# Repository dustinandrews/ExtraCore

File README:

http://authenticinvention.com/ExtraCore/
http://www.facebook.com/pages/ExtraCore-Arduino-Compatible/262175783799966

These are the Eagle files for the ExtraCore circuit board. 
License: Attribution-ShareAlike 3.0 Unported (CC BY-SA 3.0) 
http://creativecommons.org/licenses/by-sa/3.0/

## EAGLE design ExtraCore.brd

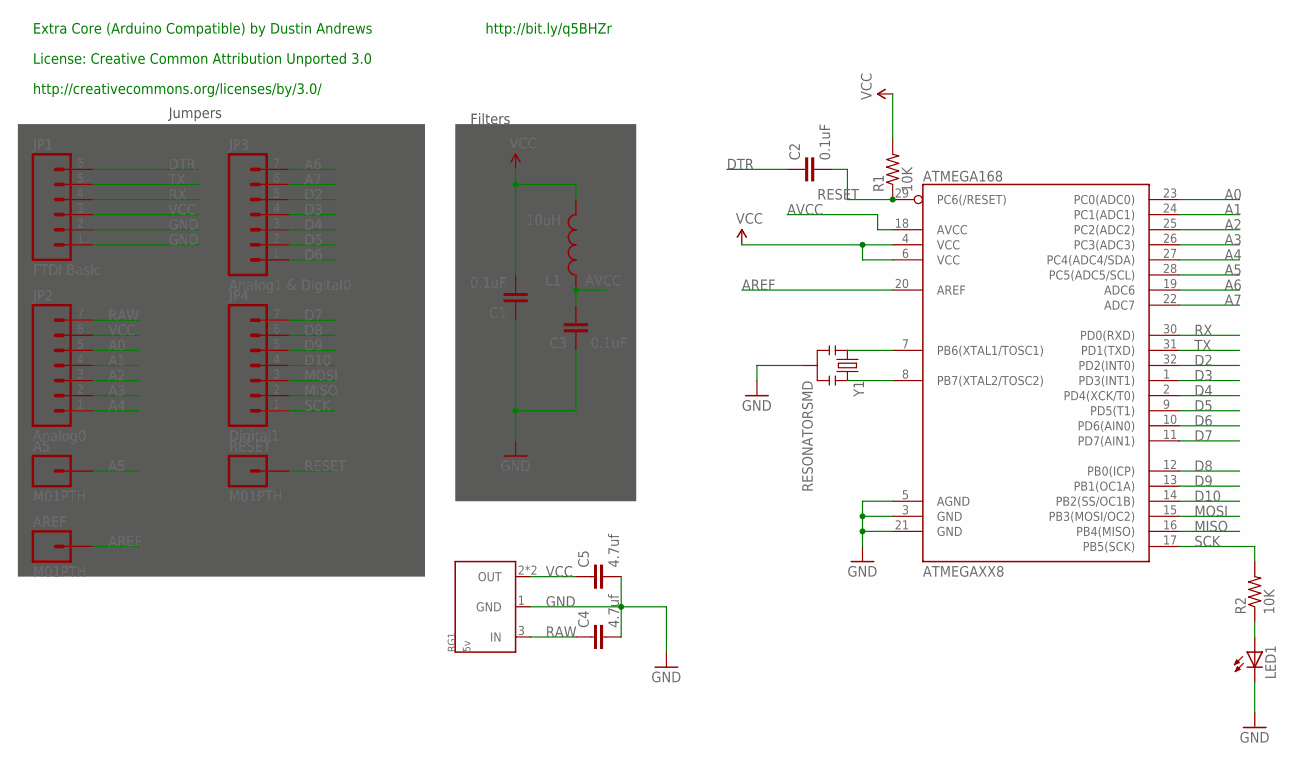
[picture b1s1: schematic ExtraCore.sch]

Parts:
A5: M01PTH; 1X01
AREF: M01PTH; 1X01
ATMEGAXX8: ATMEGA168; TQFP32-08
C1, C2, C3: 0.1uF; 0805
C4, C5: 4.7uf; 0805
JP1: FTDI Basic; 1X06
JP2: Analog0; 1X07
JP3: Analog1 & Digital0; 1X07
JP4: Digital1; 1X07
L1: 10uH; 0805
LED1: LED0805; LED-0805
R1, R2: 10K; 0805
RESET: M01PTH; 1X01
RG1: 5v; SOT223
Y1: RESONATORSMD; RESONATOR-SMD

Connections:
A0: ATMEGAXX8.23 (PC0(ADC0)), JP2.5
A1: ATMEGAXX8.24 (PC1(ADC1)), JP2.4
A2: ATMEGAXX8.25 (PC2(ADC2)), JP2.3
A3: ATMEGAXX8.26 (PC3(ADC3)), JP2.2
A4: ATMEGAXX8.27 (PC4(ADC4/SDA)), JP2.1
A5: A5.1, ATMEGAXX8.28 (PC5(ADC5/SCL))
A6: ATMEGAXX8.19 (ADC6), JP3.7
A7: ATMEGAXX8.22 (ADC7), JP3.6
AREF: AREF.1, ATMEGAXX8.20 (AREF)
AVCC: ATMEGAXX8.18 (AVCC), C3.2, L1.1
D2: ATMEGAXX8.32 (PD2(INT0)), JP3.5
D3: ATMEGAXX8.1 (PD3(INT1)), JP3.4
D4: ATMEGAXX8.2 (PD4(XCK/T0)), JP3.3
D5: ATMEGAXX8.9 (PD5(T1)), JP3.2
D6: ATMEGAXX8.10 (PD6(AIN0)), JP3.1
D7: ATMEGAXX8.11 (PD7(AIN1)), JP4.7
D8: ATMEGAXX8.12 (PB0(ICP)), JP4.6
D9: ATMEGAXX8.13 (PB1(OC1A)), JP4.5
D10: ATMEGAXX8.14 (PB2(SS/OC1B)), JP4.4
DTR: C2.1, JP1.6
GND: ATMEGAXX8.3 (GND), ATMEGAXX8.5 (AGND), ATMEGAXX8.21 (GND), C1.1, C3.1, C4.2, C5.2, JP1.1, JP1.2, LED1.C, RG1.1 (GND), Y1.2
MISO: ATMEGAXX8.16 (PB4(MISO)), JP4.2
MOSI: ATMEGAXX8.15 (PB3(MOSI/OC2)), JP4.3
unnamed: ATMEGAXX8.7 (PB6(XTAL1/TOSC1)), Y1.1
unnamed: ATMEGAXX8.8 (PB7(XTAL2/TOSC2)), Y1.3
unnamed: LED1.A, R2.1
RAW: C4.1, JP2.7, RG1.3 (IN)
RESET: ATMEGAXX8.29 (PC6(/RESET)), C2.2, R1.1, RESET.1
RX: ATMEGAXX8.30 (PD0(RXD)), JP1.4
SCK: ATMEGAXX8.17 (PB5(SCK)), JP4.1, R2.2
TX: ATMEGAXX8.31 (PD1(TXD)), JP1.5
VCC: ATMEGAXX8.4 (VCC), ATMEGAXX8.6 (VCC), C1.2, C5.1, JP1.3, JP2.6, L1.2, R1.2, RG1.2 (OUT), RG1.TAB (OUT)

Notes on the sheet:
http://creativecommons.org/licenses/by/3.0/
License: Creative Common Attribution Unported 3.0
Jumpers
Filters
Extra Core (Arduino Compatible) by Dustin Andrews
http://bit.ly/q5BHZr

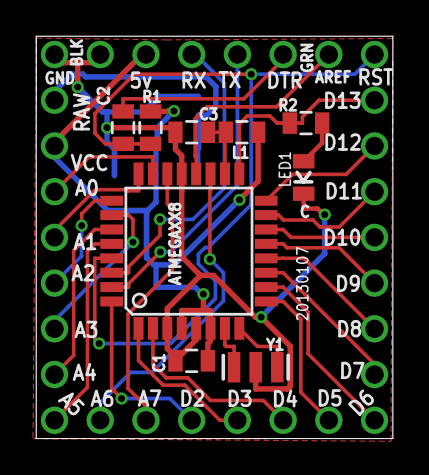
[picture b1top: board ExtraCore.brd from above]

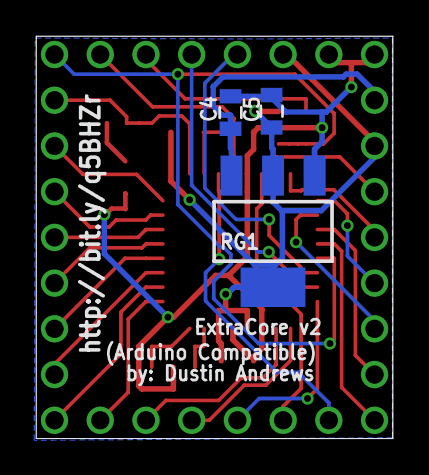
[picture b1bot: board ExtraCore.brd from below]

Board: 2 copper layers, 19.8 x 22.4 mm, 19 parts (3 on the bottom side), 32 nets.

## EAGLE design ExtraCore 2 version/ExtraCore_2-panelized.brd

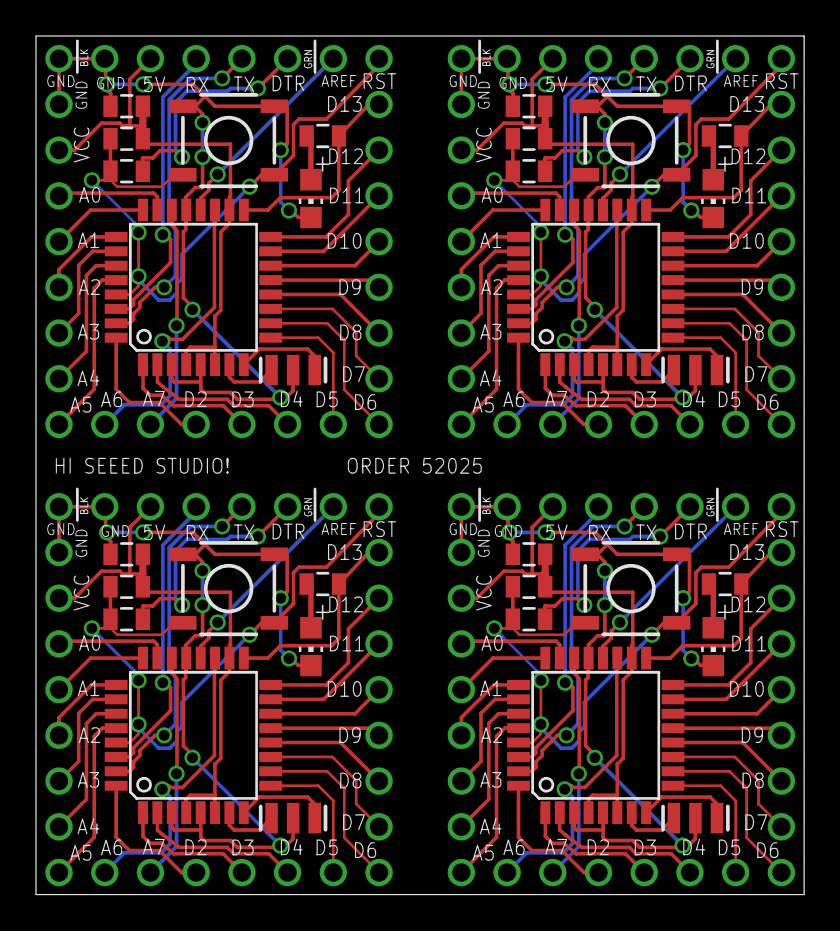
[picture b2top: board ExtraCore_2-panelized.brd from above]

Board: 2 copper layers, 42.7 x 47.7 mm, 60 parts (0 on the bottom side), 120 nets.

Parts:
A1, A2, A3, A4: M01PTH; 1X01
AREF1, AREF2, AREF3, AREF4: M01PTH; 1X01
ATMEGAXX1, ATMEGAXX2, ATMEGAXX3, ATMEGAXX4: ATMEGA168; TQFP32-08
C1, C2, C3, C4, C5, C6, C7, C8: 0.1uF; 0805
JP1, JP5, JP9, JP13: FTDI Basic; 1X06
JP2, JP6, JP10, JP14: Analog0; 1X07
JP3, JP7, JP11, JP15: Digital1; 1X07
JP4, JP8, JP12, JP16: Analog1 & Digital0; 1X07
LED1, LED2, LED3, LED4: CHIP-LED0805
R1, R2, R3, R4, R5, R6, R7, R8: 10K; 0805
RESET1, RESET2, RESET3, RESET4: M01PTH; 1X01
S1, S2, S3, S4: TACTILE_SWITCH_SMD
Y1, Y2, Y3, Y4: RESONATORSMD; RESONATOR-SMD

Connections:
A1: ATMEGAXX2.23, JP2.5
A2: ATMEGAXX2.24, JP2.4
A3: ATMEGAXX2.25, JP2.3
A4: ATMEGAXX2.26, JP2.2
A5: ATMEGAXX2.27, JP2.1
A6: A2.1, ATMEGAXX2.28
A7: ATMEGAXX2.19, JP4.7
A8: ATMEGAXX1.23, JP6.5
A9: ATMEGAXX1.24, JP6.4
A10: ATMEGAXX1.25, JP6.3
A11: ATMEGAXX1.26, JP6.2
A12: ATMEGAXX1.27, JP6.1
A13: A1.1, ATMEGAXX1.28
A14: ATMEGAXX1.19, JP8.7
A15: ATMEGAXX1.22, JP8.6
A16: ATMEGAXX2.22, JP4.6
A17: ATMEGAXX3.23, JP10.5
A18: ATMEGAXX3.24, JP10.4
A19: ATMEGAXX3.25, JP10.3
A20: ATMEGAXX3.26, JP10.2
A21: ATMEGAXX3.27, JP10.1
A22: A3.1, ATMEGAXX3.28
A23: ATMEGAXX3.19, JP12.7
A24: ATMEGAXX3.22, JP12.6
A25: ATMEGAXX4.23, JP14.5
A26: ATMEGAXX4.24, JP14.4
A27: ATMEGAXX4.25, JP14.3
A28: ATMEGAXX4.26, JP14.2
A29: ATMEGAXX4.27, JP14.1
A30: A4.1, ATMEGAXX4.28
A31: ATMEGAXX4.19, JP16.7
A32: ATMEGAXX4.22, JP16.6
AREF1: AREF1.1, ATMEGAXX1.20
AREF2: AREF2.1, ATMEGAXX2.20
AREF3: AREF3.1, ATMEGAXX3.20
AREF4: AREF4.1, ATMEGAXX4.20
D1: ATMEGAXX1.32, JP8.5
D2: ATMEGAXX2.32, JP4.5
D3: ATMEGAXX2.1, JP4.4
D4: ATMEGAXX2.2, JP4.3
D5: ATMEGAXX2.9, JP4.2
D6: ATMEGAXX2.10, JP4.1
D7: ATMEGAXX2.11, JP3.7
D8: ATMEGAXX2.12, JP3.6
D9: ATMEGAXX2.13, JP3.5
D10: ATMEGAXX2.14, JP3.4
D11: ATMEGAXX1.1, JP8.4
D12: ATMEGAXX1.2, JP8.3
D13: ATMEGAXX1.9, JP8.2
D14: ATMEGAXX1.10, JP8.1
D15: ATMEGAXX1.11, JP7.7
D16: ATMEGAXX1.12, JP7.6
D17: ATMEGAXX1.13, JP7.5
D18: ATMEGAXX1.14, JP7.4
D19: ATMEGAXX3.32, JP12.5
D20: ATMEGAXX3.1, JP12.4
D21: ATMEGAXX3.2, JP12.3
D22: ATMEGAXX3.9, JP12.2
D23: ATMEGAXX3.10, JP12.1
D24: ATMEGAXX3.11, JP11.7
D25: ATMEGAXX3.12, JP11.6
D26: ATMEGAXX3.13, JP11.5
D27: ATMEGAXX3.14, JP11.4
D28: ATMEGAXX4.32, JP16.5
D29: ATMEGAXX4.1, JP16.4
D30: ATMEGAXX4.2, JP16.3
D31: ATMEGAXX4.9, JP16.2
D32: ATMEGAXX4.10, JP16.1
D33: ATMEGAXX4.11, JP15.7
D34: ATMEGAXX4.12, JP15.6
D35: ATMEGAXX4.13, JP15.5
D36: ATMEGAXX4.14, JP15.4
DTR1: C3.1, JP5.6
DTR2: C1.1, JP1.6
DTR3: C5.1, JP9.6
DTR4: C7.1, JP13.6
GND1: ATMEGAXX1.3, ATMEGAXX1.5, ATMEGAXX1.21, C4.1, JP5.1, JP5.2, JP6.7, LED2.C, S2.1, S2.2, Y2.2
GND2: ATMEGAXX2.3, ATMEGAXX2.5, ATMEGAXX2.21, C2.1, JP1.1, JP1.2, JP2.7, LED1.C, S1.1, S1.2, Y1.2
GND3: ATMEGAXX3.3, ATMEGAXX3.5, ATMEGAXX3.21, C6.1, JP9.1, JP9.2, JP10.7, LED3.C, S3.1, S3.2, Y3.2
GND4: ATMEGAXX4.3, ATMEGAXX4.5, ATMEGAXX4.21, C8.1, JP13.1, JP13.2, JP14.7, LED4.C, S4.1, S4.2, Y4.2
MISO1: ATMEGAXX1.16, JP7.2
MISO2: ATMEGAXX2.16, JP3.2
MISO3: ATMEGAXX3.16, JP11.2
MISO4: ATMEGAXX4.16, JP15.2
MOSI1: ATMEGAXX1.15, JP7.3
MOSI2: ATMEGAXX2.15, JP3.3
MOSI3: ATMEGAXX3.15, JP11.3
MOSI4: ATMEGAXX4.15, JP15.3
unnamed: ATMEGAXX1.7, Y2.1
unnamed: ATMEGAXX1.8, Y2.3
unnamed: ATMEGAXX2.7, Y1.1
unnamed: ATMEGAXX2.8, Y1.3
unnamed: LED2.A, R4.1
unnamed: LED1.A, R2.1
unnamed: ATMEGAXX3.7, Y3.1
unnamed: ATMEGAXX3.8, Y3.3
unnamed: LED3.A, R6.1
unnamed: ATMEGAXX4.7, Y4.1
unnamed: ATMEGAXX4.8, Y4.3
unnamed: LED4.A, R8.1
RESET1: ATMEGAXX1.29, C3.2, R3.1, RESET1.1, S2.3, S2.4
RESET2: ATMEGAXX2.29, C1.2, R1.1, RESET2.1, S1.3, S1.4
RESET3: ATMEGAXX3.29, C5.2, R5.1, RESET3.1, S3.3, S3.4
RESET4: ATMEGAXX4.29, C7.2, R7.1, RESET4.1, S4.3, S4.4
RX1: ATMEGAXX1.30, JP5.4
RX2: ATMEGAXX2.30, JP1.4
RX3: ATMEGAXX3.30, JP9.4
RX4: ATMEGAXX4.30, JP13.4
SCK1: ATMEGAXX1.17, JP7.1, R4.2
SCK2: ATMEGAXX2.17, JP3.1, R2.2
SCK3: ATMEGAXX3.17, JP11.1, R6.2
SCK4: ATMEGAXX4.17, JP15.1, R8.2
TX1: ATMEGAXX1.31, JP5.5
TX2: ATMEGAXX2.31, JP1.5
TX3: ATMEGAXX3.31, JP9.5
TX4: ATMEGAXX4.31, JP13.5
VCC1: ATMEGAXX1.4, ATMEGAXX1.6, ATMEGAXX1.18, C4.2, JP5.3, JP6.6, R3.2
VCC2: ATMEGAXX2.4, ATMEGAXX2.6, ATMEGAXX2.18, C2.2, JP1.3, JP2.6, R1.2
VCC3: ATMEGAXX3.4, ATMEGAXX3.6, ATMEGAXX3.18, C6.2, JP9.3, JP10.6, R5.2
VCC4: ATMEGAXX4.4, ATMEGAXX4.6, ATMEGAXX4.18, C8.2, JP13.3, JP14.6, R7.2

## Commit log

2011-08-06 Updated design files and Gerber files
2011-08-26 Updated License to http://creativecommons.org/licenses/by-sa/3.0/
2011-09-10 Added new 0805 version files (untested). special thanks to RuggedCircuits.com.
2011-09-10 Moved some vias out from under silk screen areas
2011-09-10 Adjusted all text widths and set to vector
2011-09-10 Adjusted traces. Removed oblique angles.
2011-09-11 Edit bottom silk.
2011-09-11 Edit bottom silk some more.
2011-09-11 Added gerber files.
2011-09-11 Moved text off tstop. Split ExtraCore label and made bigger.
2012-05-31 Added ExtraCore 2 + organized files a bit
2012-06-18 Added ExtraCore RST, Eagle library and organization
2012-06-18 Removed old folder, updated README
2012-08-02 Creating ExtraCore V2.0 branch from final production files
2012-08-02 ExtraCore V2.0 with vreg and traces
2012-08-02 Added Parts List
2012-08-02 migrated to 28vqfn
2012-08-02 changed all headers to 2mm
2012-08-03 moved stuff around. It's close to routable I think.
2012-08-14 moved headers into position and routed all traces
2012-11-05 Traces and lettering for v1.5
2012-11-05 Upsated parts
2012-11-06 Touched up traces and silk.
2012-12-30 20121229 updates. Sent to manf.
2013-01-07 fixed silk
2013-01-07 updated gerbers

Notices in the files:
parts and their libraries:
SparkFun-Passives: Licensing: CC v3.0 Share-Alike You are welcome to use this library for commercial purposes.
